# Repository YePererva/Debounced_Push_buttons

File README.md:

# Module of 6 push-buttons with hardware bebouncing

This "mini-project" was inspired by [this tutorial](https://soldernerd.com/2014/11/12/switch-debouncing-using-74hc14/) and contains a few modifications:
- use either SMD ot THT buttons
- use either SMD or DIP IC
- add recommended diodes (but they are fully optional for soldering) as per [this](https://my.eng.utah.edu/~cs5780/debouncing.pdf)

## Layout and dimentions

| Top View	| Bottom View |
| ----- | ----- |
|  |  |

- overall dimensions: 1.0 in × 2.5 in
- mounting holes spacing : 0.75 in × 2.25 in
- mounting holes size : M3
- SMD sized:
	- Resistors: 0805
	- Capacitors : 0805
	- Diodes : MiniMELF

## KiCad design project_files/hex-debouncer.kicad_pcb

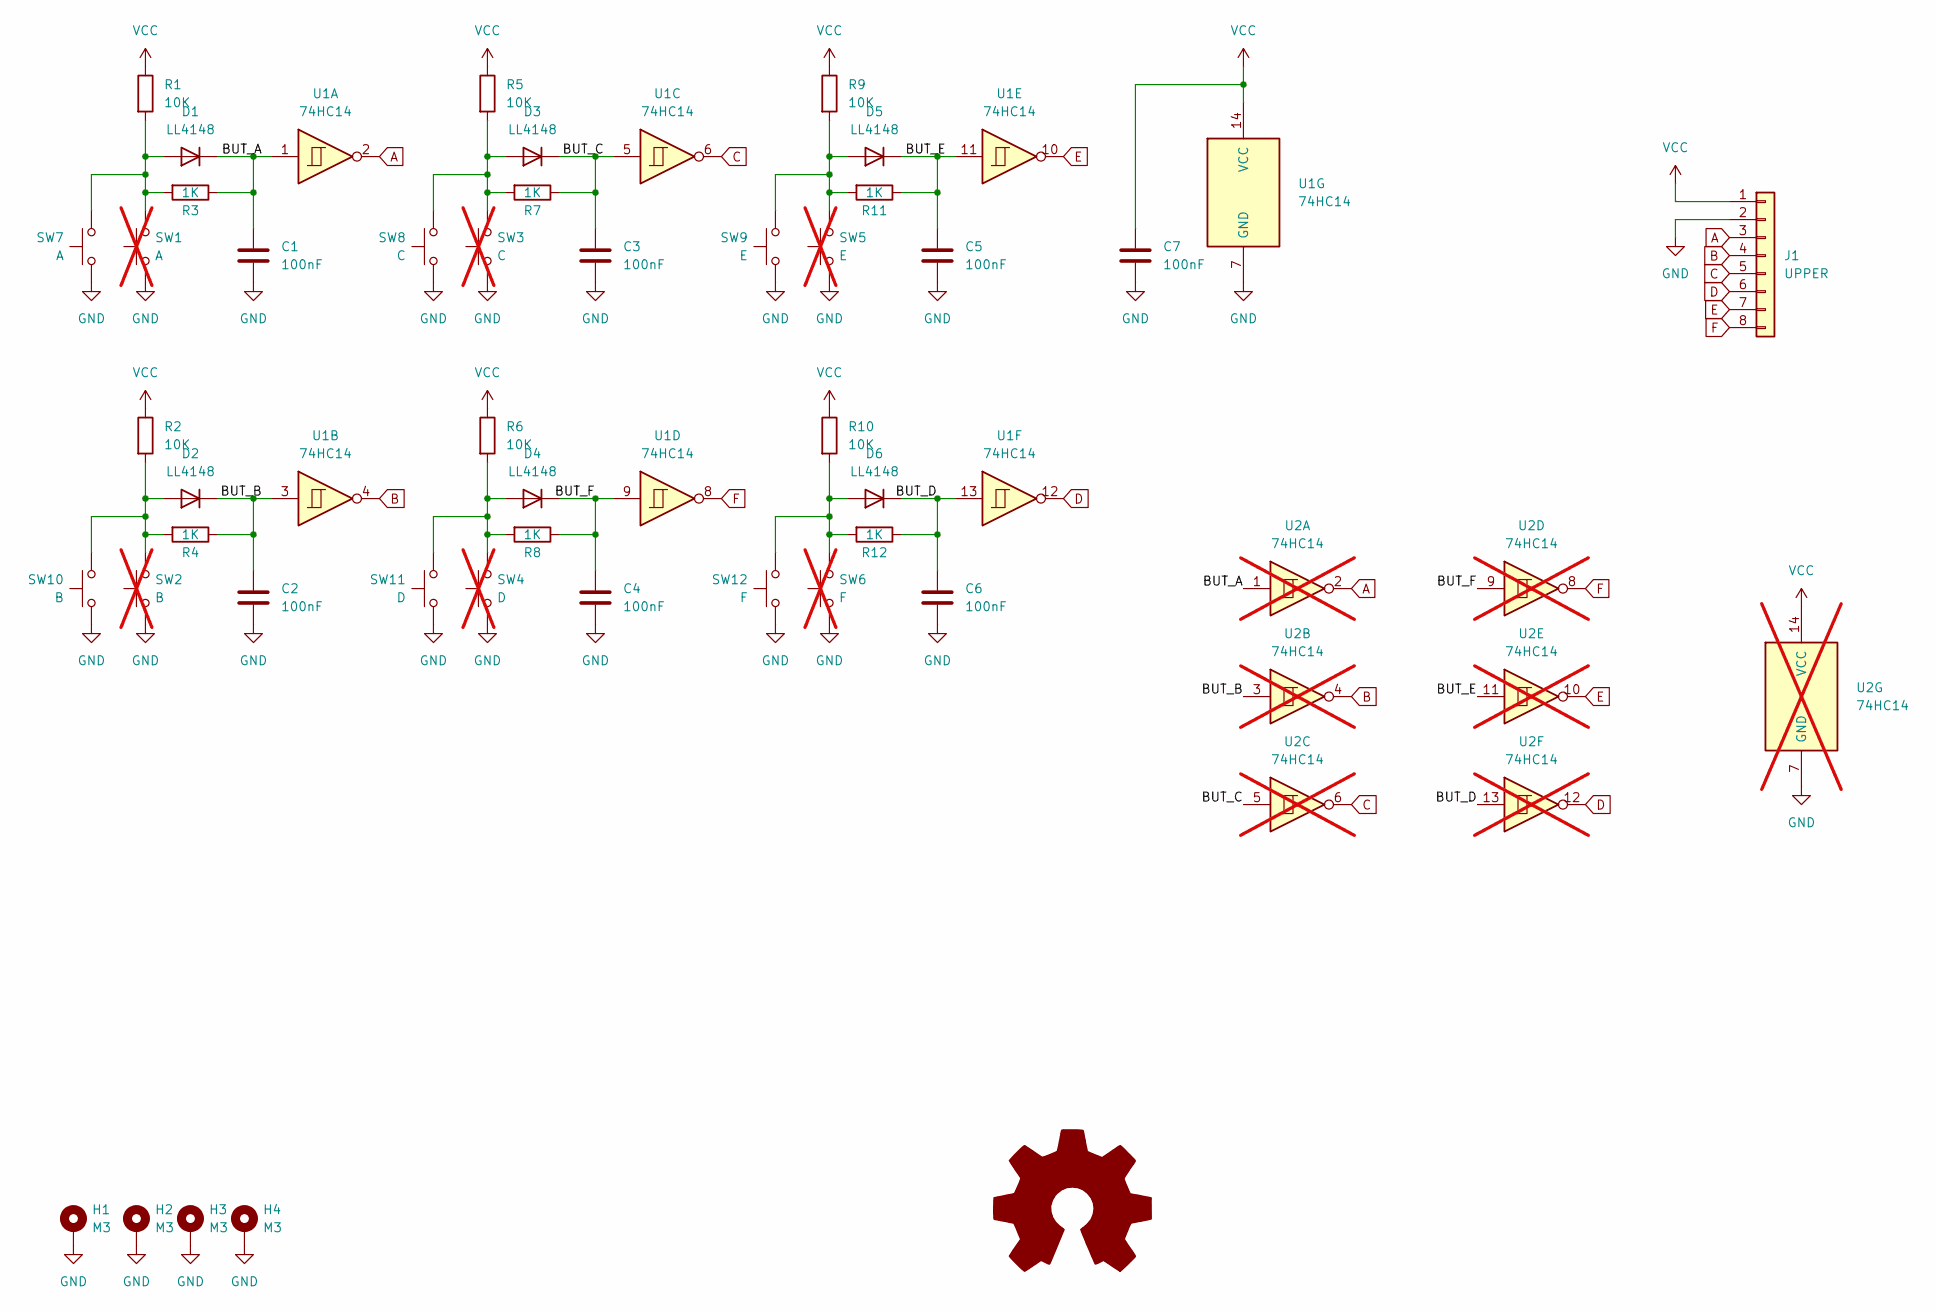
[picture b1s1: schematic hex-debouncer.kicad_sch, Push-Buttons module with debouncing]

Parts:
C1, C2, C3, C4, C5, C6, C7: 100nF; C_0805_2012Metric
D1, D2, D3, D4, D5, D6: LL4148; D_MiniMELF
H1, H2, H3, H4: M3; MountingHole_3.2mm_M3_DIN965_Pad_TopBottom
J1: UPPER; PinHeader_1x08_P2.54mm_Vertical
R1, R2, R5, R6, R9, R10: 10K; R_0805_2012Metric
R3, R4, R7, R8, R11, R12: 1K; R_0805_2012Metric
SW1: A; SW_SPST_PTS645; not fitted
SW2: B; SW_SPST_PTS645; not fitted
SW3: C; SW_SPST_PTS645; not fitted
SW4: D; SW_SPST_PTS645; not fitted
SW5: E; SW_SPST_PTS645; not fitted
SW6: F; SW_SPST_PTS645; not fitted
SW7: A; SW_PUSH_6mm_H8mm
SW8: C; SW_PUSH_6mm_H8mm
SW9: E; SW_PUSH_6mm_H8mm
SW10: B; SW_PUSH_6mm_H8mm
SW11: D; SW_PUSH_6mm_H8mm
SW12: F; SW_PUSH_6mm_H8mm
U1: 74HC14; SO-14_3.9x8.65mm_P1.27mm
U2: 74HC14; DIP-14_W7.62mm; not fitted

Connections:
/BUT_A: C1.1, D1.1 (K), R3.1, U1.1, U2.1
/BUT_B: C2.1, D2.1 (K), R4.1, U1.3, U2.3
/BUT_C: C3.1, D3.1 (K), R7.1, U1.5, U2.5
/BUT_D: C6.1, D6.1 (K), R12.1, U1.13, U2.13
/BUT_E: C5.1, D5.1 (K), R11.1, U1.11, U2.11
/BUT_F: C4.1, D4.1 (K), R8.1, U1.9, U2.9
A: J1.3, U1.2, U2.2
B: J1.4, U1.4, U2.4
C: J1.5, U1.6, U2.6
D: J1.6, U1.12, U2.12
E: J1.7, U1.10, U2.10
F: J1.8, U1.8, U2.8
GND: C1.2, C2.2, C3.2, C4.2, C5.2, C6.2, C7.2, H1.1, H2.1, H3.1, H4.1, J1.2, SW1.1, SW2.1, SW3.1, SW4.1, SW5.1, SW6.1, SW7.1, SW8.1, SW9.1, SW10.1, SW11.1, SW12.1, U1.7 (GND), U2.7 (GND)
unnamed: D1.2 (A), R1.2, R3.2, SW1.2, SW7.2
unnamed: D2.2 (A), R2.2, R4.2, SW2.2, SW10.2
unnamed: D3.2 (A), R5.2, R7.2, SW3.2, SW8.2
unnamed: D4.2 (A), R6.2, R8.2, SW4.2, SW11.2
unnamed: D5.2 (A), R9.2, R11.2, SW5.2, SW9.2
unnamed: D6.2 (A), R10.2, R12.2, SW6.2, SW12.2
VCC: C7.1, J1.1, R1.1, R2.1, R5.1, R6.1, R9.1, R10.1, U1.14 (VCC), U2.14 (VCC)

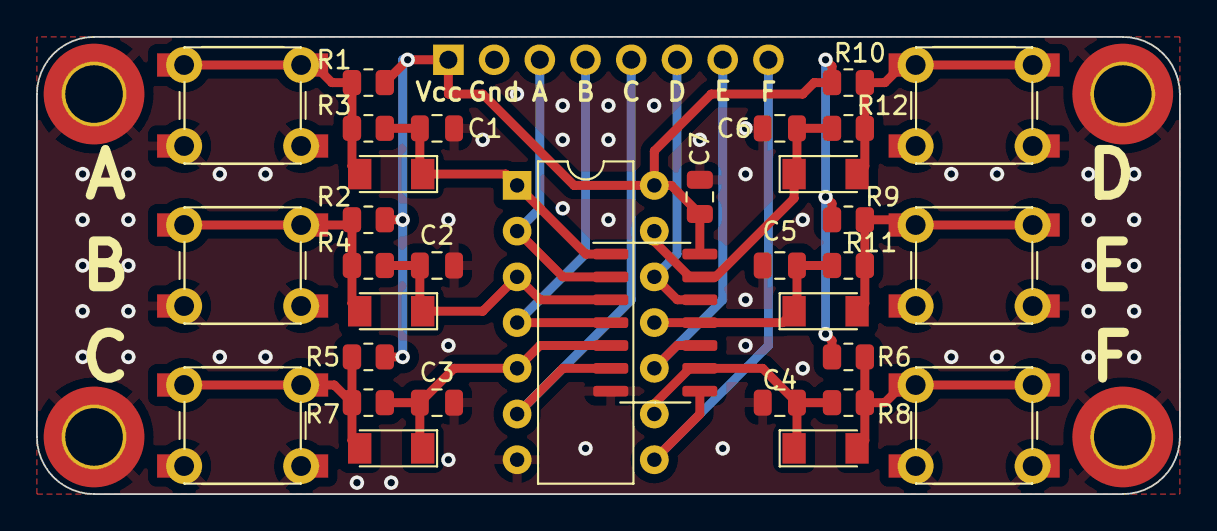
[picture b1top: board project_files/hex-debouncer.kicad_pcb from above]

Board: 2 copper layers, 63.5 x 25.4 mm, 44 parts (1 on the bottom side), 20 nets.

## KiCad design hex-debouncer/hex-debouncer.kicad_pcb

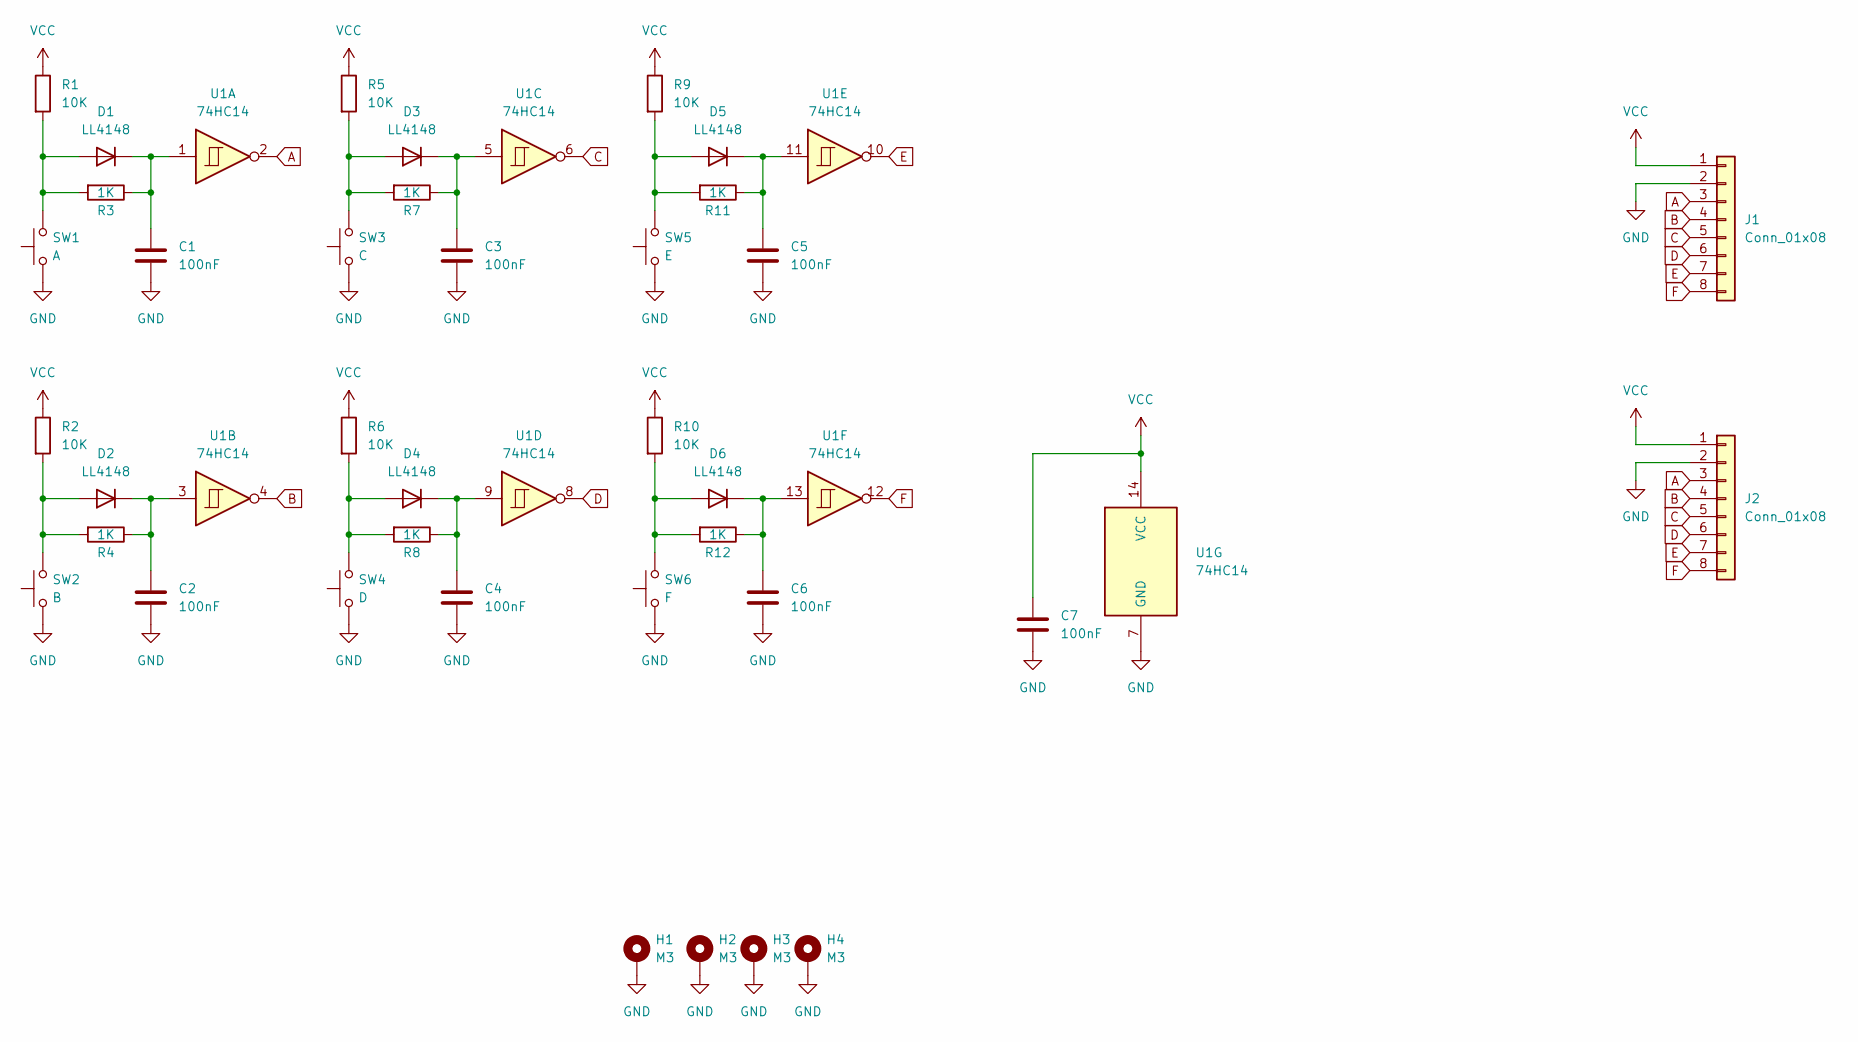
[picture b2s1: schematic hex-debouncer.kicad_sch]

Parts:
C1, C2, C3, C4, C5, C6, C7: 100nF; C_0805_2012Metric
D1, D2, D3, D4, D5, D6: LL4148; D_MiniMELF
H1, H2, H3, H4: M3; MountingHole_3.2mm_M3_DIN965_Pad_TopBottom
J1, J2: Conn_01x08; PinHeader_1x08_P2.54mm_Vertical
R1, R2, R5, R6, R9, R10: 10K; R_0805_2012Metric
R3, R4, R7, R8, R11, R12: 1K; R_0805_2012Metric
SW1: A; SW_SPST_PTS645
SW2: B; SW_SPST_PTS645
SW3: C; SW_SPST_PTS645
SW4: D; SW_SPST_PTS645
SW5: E; SW_SPST_PTS645
SW6: F; SW_SPST_PTS645
U1: 74HC14; SO-14_3.9x8.65mm_P1.27mm

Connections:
A: J1.3, J2.3, U1.2
B: J1.4, J2.4, U1.4
C: J1.5, J2.5, U1.6
D: J1.6, J2.6, U1.8
E: J1.7, J2.7, U1.10
F: J1.8, J2.8, U1.12
GND: C1.2, C2.2, C3.2, C4.2, C5.2, C6.2, C7.2, H1.1, H2.1, H3.1, H4.1, J1.2, J2.2, SW1.1, SW2.1, SW3.1, SW4.1, SW5.1, SW6.1, U1.7 (GND)
unnamed: C1.1, D1.1 (K), R3.1, U1.1
unnamed: C2.1, D2.1 (K), R4.1, U1.3
unnamed: C3.1, D3.1 (K), R7.1, U1.5
unnamed: C4.1, D4.1 (K), R8.1, U1.9
unnamed: C5.1, D5.1 (K), R11.1, U1.11
unnamed: C6.1, D6.1 (K), R12.1, U1.13
unnamed: D1.2 (A), R1.2, R3.2, SW1.2
unnamed: D2.2 (A), R2.2, R4.2, SW2.2
unnamed: D3.2 (A), R5.2, R7.2, SW3.2
unnamed: D4.2 (A), R6.2, R8.2, SW4.2
unnamed: D5.2 (A), R9.2, R11.2, SW5.2
unnamed: D6.2 (A), R10.2, R12.2, SW6.2
VCC: C7.1, J1.1, J2.1, R1.1, R2.1, R5.1, R6.1, R9.1, R10.1, U1.14 (VCC)

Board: 2 copper layers, 38 parts (1 on the bottom side), 20 nets, no tracks yet.

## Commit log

2022-08-28 initial thoughts
2024-02-24 Converted to KiCAD8
2024-05-29 FInalized layout
2024-05-29 Added Readme
2024-05-29 Image editing
2024-06-01 rerouted with 0.5 mm tracks
